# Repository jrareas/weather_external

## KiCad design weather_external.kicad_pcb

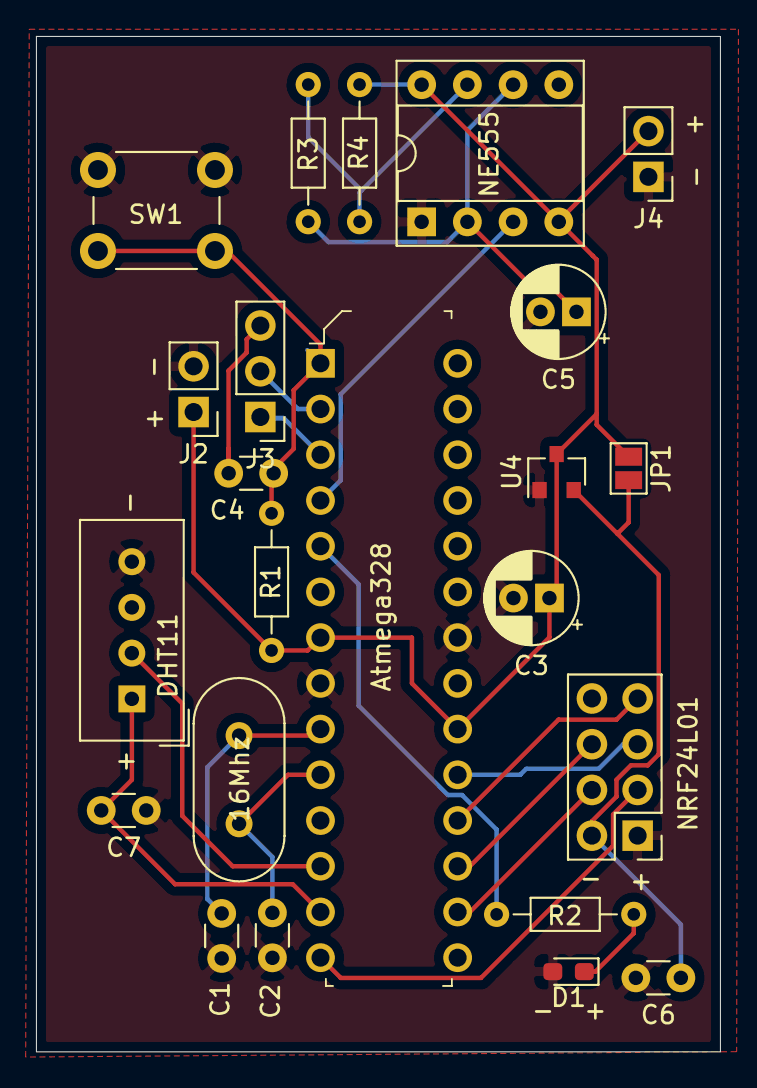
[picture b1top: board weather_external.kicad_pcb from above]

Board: 2 copper layers, 38.0 x 56.4 mm, 23 parts (0 on the bottom side), 21 nets.

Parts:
16Mhz: Crystal; Crystal_HC18-U_Vertical
Atmega328: ATMEGA328-PU; DIP-28_W7.62mm
C1, C2, C4, C6, C7: C; C_Disc_D3.0mm_W1.6mm_P2.50mm
C3: 10nf; CP_Radial_D5.0mm_P2.00mm
C5: CP; CP_Radial_D5.0mm_P2.00mm
D1: LED; LED_0603_1608Metric_Pad1.05x0.95mm_HandSolder
DHT11: DHT11; Aosong_DHT11_5.5x12.0_P2.54mm
J2, J4: 22-23-2021; PinHeader_1x02_P2.54mm_Vertical
J3: 640456-3; PinHeader_1x03_P2.54mm_Vertical
JP1: Jumper; SolderJumper-2_P1.3mm_Open_Pad1.0x1.5mm
NE555: NE555DR; DIP-8_W7.62mm_Socket
NRF24L01: Conn_02x04_Odd_Even; PinHeader_2x04_P2.54mm_Vertical
R1: 10k; R_Axial_DIN0204_L3.6mm_D1.6mm_P7.62mm_Horizontal
R2, R3: 220; R_Axial_DIN0204_L3.6mm_D1.6mm_P7.62mm_Horizontal
R4: 1M; R_Axial_DIN0204_L3.6mm_D1.6mm_P7.62mm_Horizontal
SW1: SW_Push; SW_PUSH_6mm_H7.3mm
U4: MCP1700-3302E_SOT23; SOT-23

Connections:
GND: Atmega328.8, Atmega328.22, C1.2, C2.1, C3.2, C5.2, C6.2, C7.1, D1.2, DHT11.4, J2.2, J4.1, NE555.1, NRF24L01.1, SW1.1, U4.1
unnamed: 16Mhz.1, Atmega328.9, C1.1
unnamed: 16Mhz.2, Atmega328.10, C2.2
unnamed: Atmega328.1, C4.1, R1.2, SW1.2
unnamed: C4.2, J3.3
unnamed: C5.1, NE555.2, NE555.6, R3.2
unnamed: C6.1, JP1.2, NRF24L01.2, U4.2
unnamed: Atmega328.13, C7.2, DHT11.1
unnamed: D1.1, R2.2
unnamed: Atmega328.3, J3.1
unnamed: Atmega328.2, J3.2
unnamed: Atmega328.14, NRF24L01.3
unnamed: Atmega328.16, NRF24L01.4
unnamed: Atmega328.19, NRF24L01.5
unnamed: Atmega328.17, NRF24L01.6
unnamed: Atmega328.18, NRF24L01.7
unnamed: Atmega328.5, R2.1
unnamed: NE555.7, R3.1, R4.2
unnamed: Atmega328.4, NE555.3
unnamed: Atmega328.12, DHT11.2
VCC: Atmega328.7, Atmega328.20, C3.1, J2.1, J4.2, JP1.1, NE555.4, NE555.8, R1.1, R4.1, U4.3

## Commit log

2020-10-03 Print version 1
2020-10-04 Weather External v1.0
